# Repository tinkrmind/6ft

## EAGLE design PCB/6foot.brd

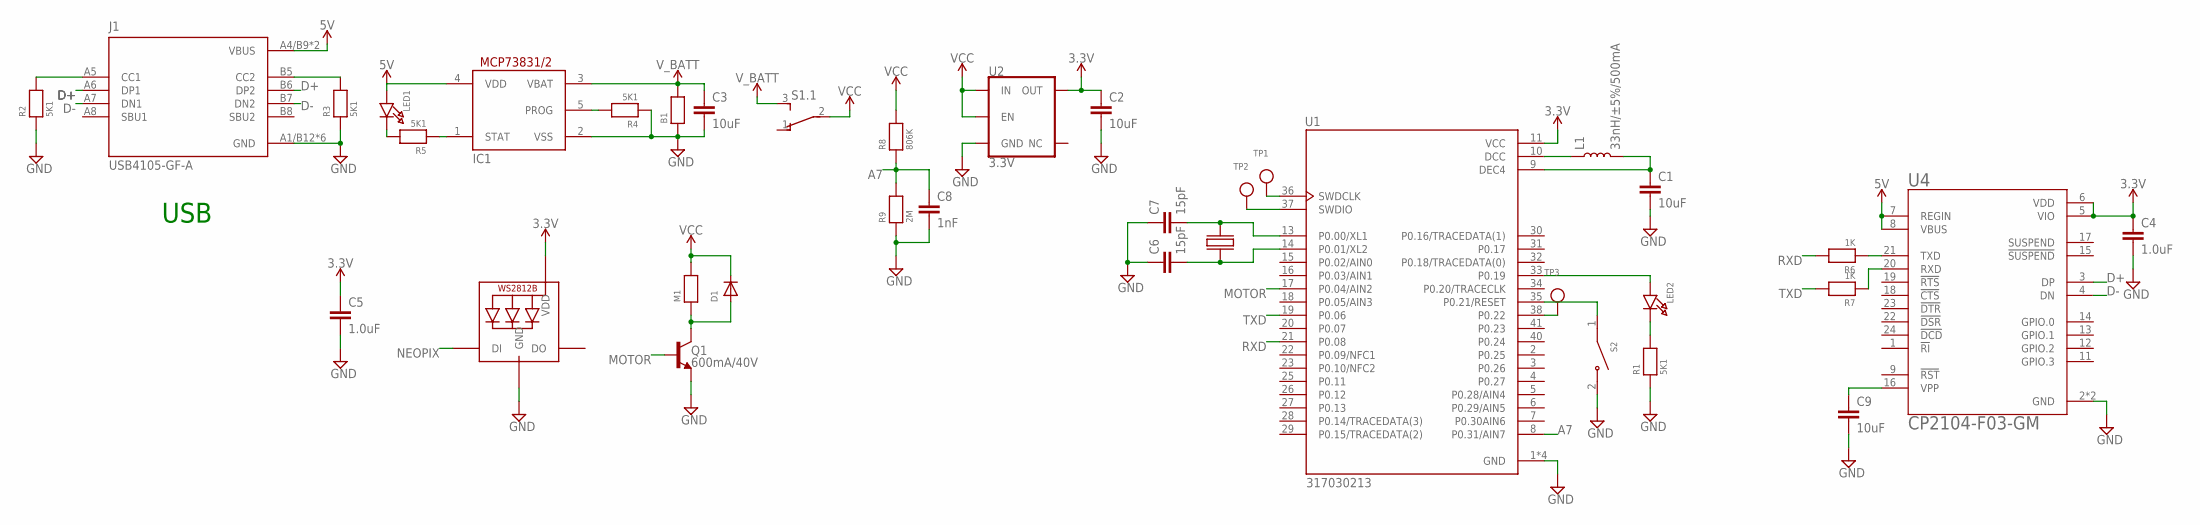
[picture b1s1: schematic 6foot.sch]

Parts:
B1: RESISTOR1206; 1206
C1, C2, C3, C9: 10uF; 1206
C4, C5: 1.0uF; 0603
C6, C7: 15pF; 0603
C8: 1nF; 0603
D1: DIODESOD-323F; SOD-323F
IC1: MCP73831/OT; SOT23-5L
J1: USB4105-GF-A; GCT_USB4105-GF-A
L1: 33nH/±5%/500mA; 0603
LED1, LED2: LED0603; CHIPLED_0603
LED3: WS2812B5050; WS2812B
M1: RESISTOR1206; 1206
Q1: 600mA/40V; SOT23-3
R1, R2, R3, R4, R5: 5K1; 0603
R6, R7: 1K; 0603
R8: 806K; 0603
R9: 2M; 0603
S1: JS202011JCQN
S2: PTS636_SM43J_SMTR_LFS; SW_PTS636_SM43J_SMTR_LFS
TP1, TP2, TP3: TESTPOINTROUND2MM; TESTPOINT_ROUND_2MM
U1: 317030213; XCVR_317030213
U2: 3.3V; SOT23-5
U4: CP2104-F03-GM; QFN50P400X400X80-25N
U$1: XTAL_32KHZ

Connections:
3.3V: C2.1, C4.1, C5.1, LED3.1-VDD (VDD), U1.11 (VCC), U2.5 (OUT), U4.5 (VIO), U4.6 (VDD)
5V: J1.A4/B9 (VBUS), J1.B4/A9 (VBUS), U4.7 (REGIN), U4.8 (VBUS)
A7: C8.1, R8.1, R9.2, U1.8 (P0.31/AIN7)
D+: J1.A6 (DP1), J1.B6 (DP2), U4.3 (DP)
D-: J1.A7 (DN1), J1.B7 (DN2), U4.4 (DN)
GND: B1.1, C1.2, C2.2, C3.2, C4.2, C5.2, C6.1, C7.1, C8.2, C9.2, IC1.2 (VSS), J1.A1/B12 (GND), J1.B1/A12 (GND), J1.G1 (GND), J1.G2 (GND), J1.G3 (GND), J1.G4 (GND), LED3.3-GND (GND), Q1.2 (E), R1.1, R2.1, R3.1, R4.1, R9.1, S2.2 (NO), U1.1 (GND), U1.12 (GND), U1.24 (GND), U1.39 (GND), U2.2 (GND), U4.2 (GND), U4.25 (GND)
MOTOR: Q1.1 (B), U1.17 (P0.04/AIN2)
unnamed: C7.2, U1.13 (P0.00/XL1), U$1.P$2
unnamed: C6.2, U1.14 (P0.01/XL2), U$1.P$1
unnamed: J1.A5 (CC1), R2.2
unnamed: L1.1, U1.10 (DCC)
unnamed: C1.1, L1.2, U1.9 (DEC4)
unnamed: J1.B5 (CC2), R3.2
unnamed: IC1.5 (PROG), R4.2
unnamed: D1.A, M1.1, Q1.3 (C)
unnamed: LED2.A, U1.33 (P0.19)
unnamed: IC1.1 (STAT), R5.1
unnamed: LED1.C, R5.2
unnamed: IC1.4 (VDD), LED1.A
unnamed: LED2.C, R1.2
unnamed: C9.1, U4.16 (VPP)
unnamed: R6.1, U4.21 (TXD)
unnamed: S2.1 (COM), U1.35 (P0.21/RESET)
unnamed: TP3.P$1, U1.38 (P0.22)
unnamed: TP1.P$1, U1.36 (SWDCLK)
unnamed: TP2.P$1, U1.37 (SWDIO)
NEOPIX: LED3.4-DIN (DI)
RXD: R6.2, U1.21 (P0.08)
TXD: R7.1, R7.2, U1.19 (P0.06), U4.20 (RXD)
VCC: D1.C, M1.2, R8.2, S1.2, U2.1 (IN), U2.3 (EN)
V_BATT: B1.2, C3.1, IC1.3 (VBAT), S1.3 (S)

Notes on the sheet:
USB

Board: 2 copper layers, 37 parts (0 on the bottom side), 30 nets, no tracks yet.

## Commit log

2020-05-09 Starting collab w/ Cedric. Bluetooth RSSI motor buzzing working on bluefruit.
2020-05-09 Added Yeseul's code
2020-05-09 Added WIP PCB files. Might not be continued if Smartband project is successful.
2023-02-14 [ImgBot] Optimize images
    *Total -- 4,395.03kb -> 4,276.69kb (2.69%)
    /Adafruit feather bluefruit/microcontrollers_revgsch.png -- 70.79kb -> 41.75kb (41.02%)
    /SmartBand/extra/saving_face.gif -- 4,324.24kb -> 4,234.94kb (2.07%)

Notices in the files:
parts and their libraries:
SparkFun-Capacitors: Licensing: Creative Commons ShareAlike 4.0 International - https://creativecommons.org/licenses/by-sa/4.0
microbuilder: This work is placed in the public domain, and may be freely used for commercial and non-commercial work with the following conditions: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
